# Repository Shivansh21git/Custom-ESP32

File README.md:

# 🚀 Custom ESP32 Development Board – Designed in KiCad

Welcome to the hardware design repo of a **fully custom ESP32-WROOM-32 development board**, engineered for rapid prototyping, compact integration, and modern embedded applications. Designed from the ground up using **KiCad**, this board blends functionality, minimalism, and scalability in one neat package.

---

## ✨ Key Features

- 🔌 **USB Type-C** interface with ESD protection and auto-reset
- 📡 **ESP32-WROOM-32** SoC (Wi-Fi + BLE, dual-core MCU)
- 🔋 **Onboard 3.3V LDO** regulator for stable low-noise operation
- 🎛️ **Accessible I/O headers**: UART, SPI, I2C, ADC, DAC, and GPIOs
- 📐 **Compact PCB layout** – Breadboard compatible
- 🛡️ **Proper antenna clearance & keep-out zone**
- 💾 Designed 100% in **KiCad 7.x**

---

## 🧠 Technical Overview

| Component         | Details                                             |
|------------------|-----------------------------------------------------|
| **MCU**          | ESP32-WROOM-32 (ESP32-D0WDQ6)                       |
| **USB Interface**| USB-C (via CH340/CP2102 + reset circuit)            |
| **Power Input**  | 5V via USB-C                                        |
| **Voltage Reg.** | AP2112 / AMS1117-3.3 LDO Regulator                  |
| **Reset Circuit**| BOOT & EN push buttons with RC logic                |
| **Connectivity** | UART, I2C, SPI, ADC, DAC, PWM exposed               |
| **Mounting**     | 2x M2 screw holes for enclosure compatibility       |
| **Board Size**   | ~74mm x 32mm                                        |

---

---

## 🛠️ Getting Started

### 🖥️ Open Project
- Clone this repo and open `custom_esp32.kicad_pro` in **KiCad 7.x**

### 🧾 Generate Gerbers
- Go to **File → Plot** → Generate files for your PCB manufacturer

### 🔧 Program the Board
- Use Arduino IDE / ESP-IDF
- Connect via USB-C
- Use `BOOT` + `EN` buttons for flashing if needed

---

## 📦 Fabrication Tips

- Board designed with **antenna clearance**
- Clean **silkscreen labeling** for easy assembly
- No component under USB port for low-profile casing
- Test points can be added if needed for production

---

## 💡 Applications

- IoT Device Development
- Sensor Gateway Nodes
- Home Automation
- Robotics Controller
- Custom Wireless Modules

---

## 🤝 Credits & Contact

Designed by **Shivansh Chauhan**  
📧 Email: `shivanshchauhan.228@gmail.com`  
🔗 LinkedIn: https://www.linkedin.com/in/shivanshchauhan2001

If you like this project, consider giving it a ⭐ on GitHub!

---

> “Great hardware begins with thoughtful design.”

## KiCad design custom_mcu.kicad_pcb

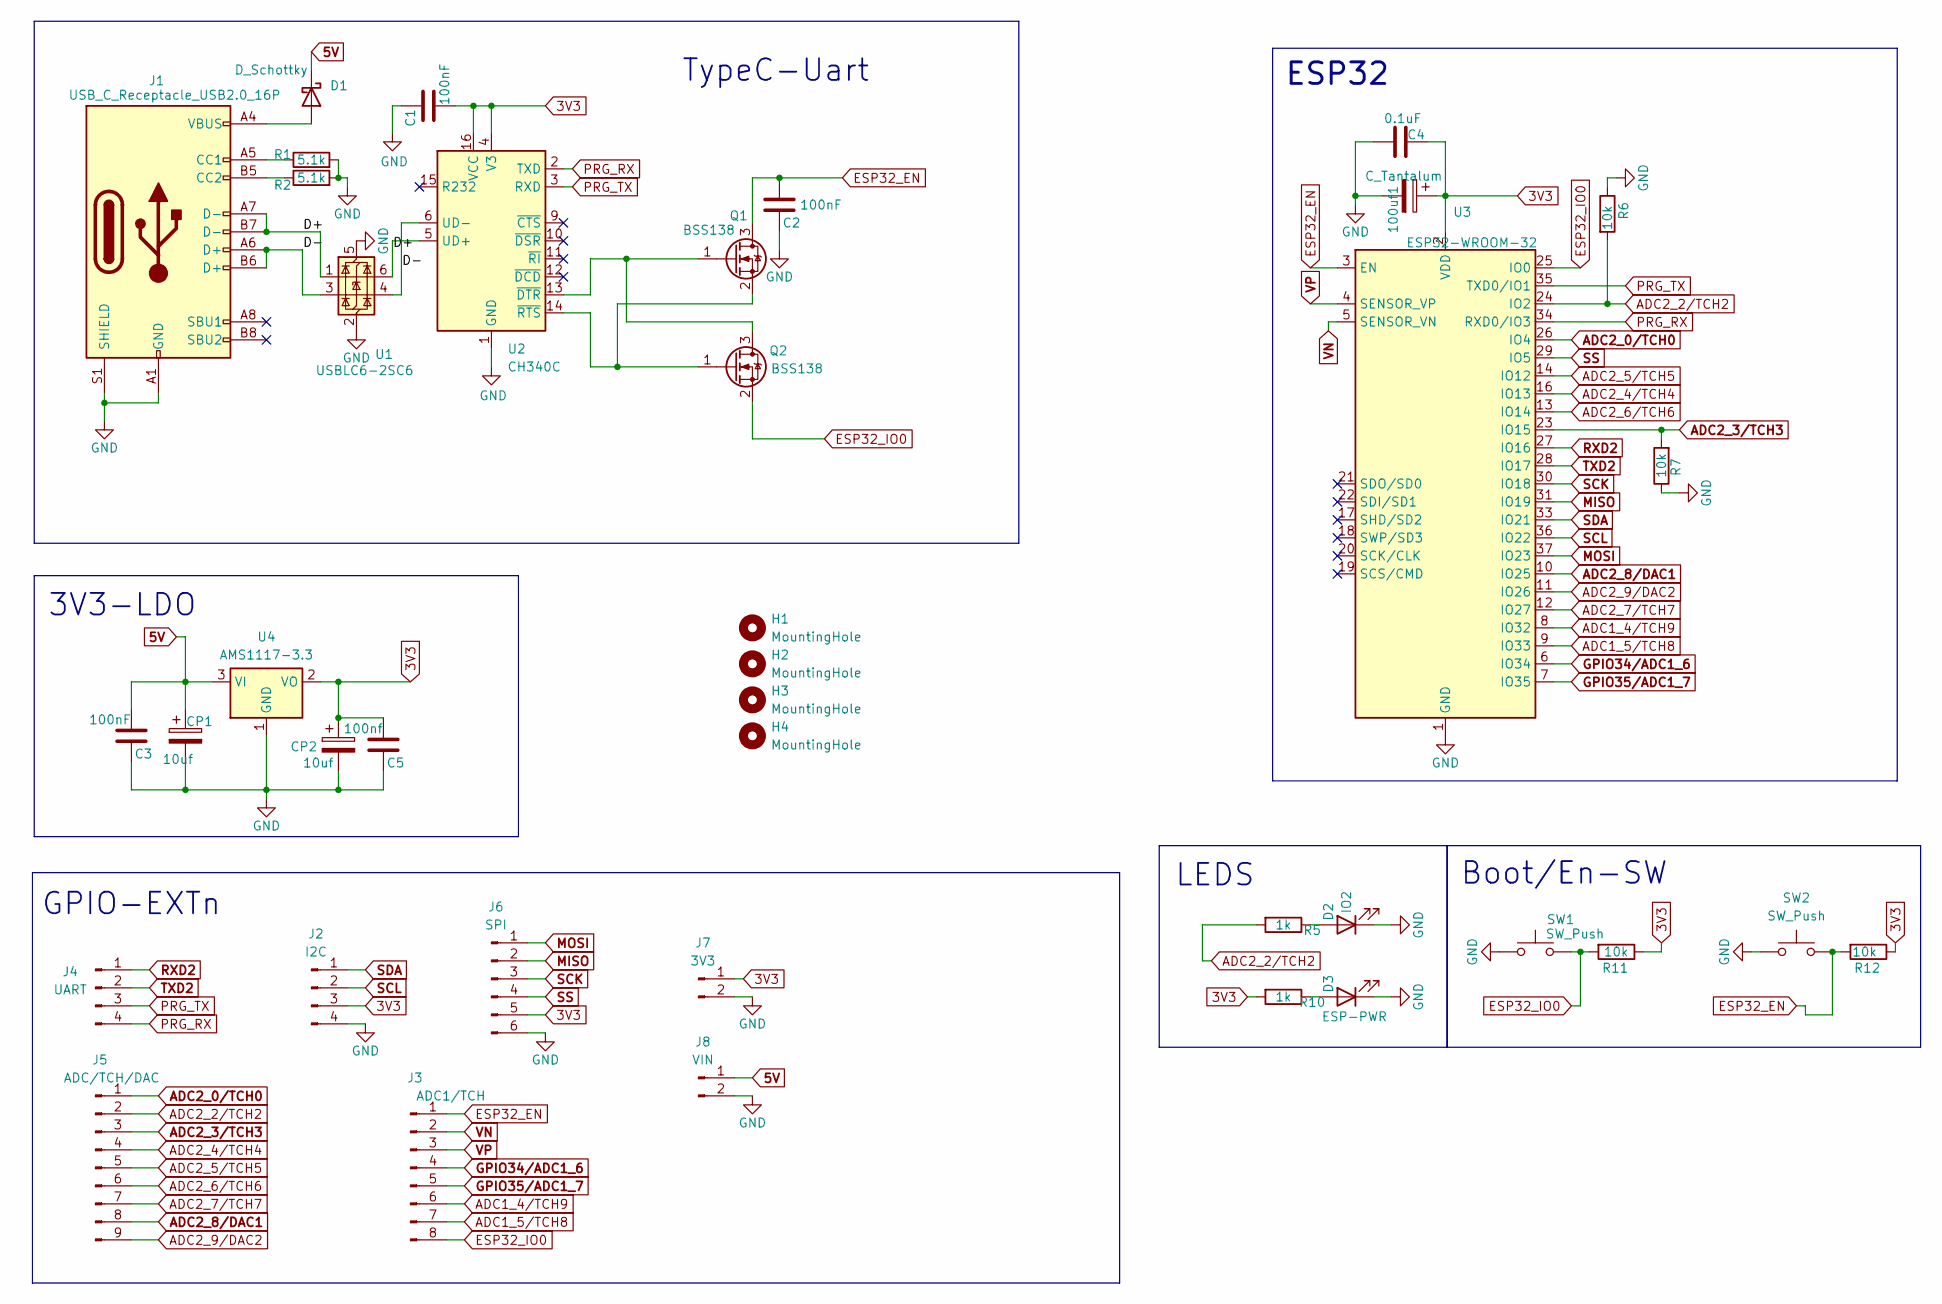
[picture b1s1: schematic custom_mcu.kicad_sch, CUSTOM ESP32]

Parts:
100uf1: C_Tantalum; CP_EIA-3216-10_Kemet-I
C1, C2, C3: 100nF; C_0805_2012Metric_Pad1.18x1.45mm_HandSolder
C4: 0.1uF; C_0805_2012Metric_Pad1.18x1.45mm_HandSolder
C5: 100nf; C_0805_2012Metric_Pad1.18x1.45mm_HandSolder
CP1, CP2: 10uf; C_0805_2012Metric_Pad1.18x1.45mm_HandSolder
D1: D_Schottky; R_0805_2012Metric_Pad1.20x1.40mm_HandSolder
D2: IO2; LED_0805_2012Metric_Pad1.15x1.40mm_HandSolder
D3: ESP-PWR; LED_0805_2012Metric_Pad1.15x1.40mm_HandSolder
H1, H2, H3, H4: MountingHole; MountingHole_2.2mm_M2
J1: USB_C_Receptacle_USB2.0_16P; USB_C_Receptacle_GCT_USB4105-xx-A_16P_TopMnt_Horizontal
J2: I2C; PinHeader_1x04_P2.54mm_Vertical
J3: ADC1/TCH; PinHeader_1x08_P2.54mm_Vertical
J4: UART; PinHeader_1x04_P2.54mm_Vertical
J5: ADC/TCH/DAC; PinHeader_1x09_P2.54mm_Vertical
J6: SPI; PinHeader_1x06_P2.54mm_Vertical
J7: 3V3; PinHeader_1x02_P2.54mm_Vertical
J8: VIN; PinHeader_1x02_P2.54mm_Vertical
Q1, Q2: BSS138; SOT-23
R1, R2: 5.1k; R_0805_2012Metric_Pad1.20x1.40mm_HandSolder
R5, R10: 1k; R_0805_2012Metric_Pad1.20x1.40mm_HandSolder
R6, R7, R11, R12: 10k; R_0805_2012Metric_Pad1.20x1.40mm_HandSolder
SW1, SW2: SW_Push; SW_Tactile_SPST_NO_Straight_CK_PTS636Sx25SMTRLFS
U1: USBLC6-2SC6; SOT-23-6
U2: CH340C; SOIC-16_3.9x9.9mm_P1.27mm
U3: ESP32-WROOM-32
U4: AMS1117-3.3; SOT-223-3_TabPin2

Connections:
3V3: 100uf1.1, C1.2, C4.2, C5.2, CP2.1, J2.3, J6.5, J7.1, R10.2, R11.1, R12.1, U2.4 (V3), U2.16 (VCC), U3.2 (VDD), U4.2 (VO)
5V: C3.2, CP1.1, D1.1 (K), J8.1, U4.3 (VI)
/D+: J1.A7 (D-), J1.B7 (D-), U1.1 (I/O1), U1.6 (I/O1), U2.5 (UD+)
/D-: J1.A6 (D+), J1.B6 (D+), U1.3 (I/O2), U1.4 (I/O2), U2.6 (UD-)
ADC1_4/TCH9: J3.6, U3.8 (IO32)
ADC1_5/TCH8: J3.7, U3.9 (IO33)
ADC2_0/TCH0: J5.1, U3.26 (IO4)
ADC2_2/TCH2: J5.2, R5.2, R6.2, U3.24 (IO2)
ADC2_3/TCH3: J5.3, R7.2, U3.23 (IO15)
ADC2_4/TCH4: J5.4, U3.16 (IO13)
ADC2_5/TCH5: J5.5, U3.14 (IO12)
ADC2_6/TCH6: J5.6, U3.13 (IO14)
ADC2_7/TCH7: J5.7, U3.12 (IO27)
ADC2_8/DAC1: J5.8, U3.10 (IO25)
ADC2_9/DAC2: J5.9, U3.11 (IO26)
ESP32_EN: C2.2, J3.1, Q1.3 (D), R12.2, SW2.2, U3.3 (EN); also elsewhere on the board
ESP32_IO0: J3.8, Q2.2 (S), R11.2, SW1.2, U3.25 (IO0)
GND: 100uf1.2, C1.1, C2.1, C3.1, C4.1, C5.1, CP1.2, CP2.2, D2.1 (K), D3.1 (K), J1.A1 (GND), J1.A12 (GND), J1.B1 (GND), J1.B12 (GND), J1.S1 (SHIELD), J2.4, J6.6, J7.2, J8.2, R1.2, R2.2, R6.1, R7.1, SW1.1, SW2.1, U1.2 (GND), U1.5 (VBUS), U2.1 (GND), U3.1 (GND), U3.15 (GND), U3.38 (GND), U3.39 (GND), U4.1 (GND); also elsewhere on the board
GPIO34/ADC1_6: J3.4, U3.6 (IO34)
GPIO35/ADC1_7: J3.5, U3.7 (IO35)
MISO: J6.2, U3.31 (IO19)
MOSI: J6.1, U3.37 (IO23)
unnamed: D1.2 (A), J1.A4 (VBUS), J1.A9 (VBUS), J1.B4 (VBUS), J1.B9 (VBUS)
unnamed: D2.2 (A), R5.1
unnamed: D3.2 (A), R10.1
unnamed: J1.A5 (CC1), R1.1
unnamed: J1.B5 (CC2), R2.1
unnamed: Q1.1 (G), Q2.3 (D), U2.13 (~DTR)
unnamed: Q1.2 (S), Q2.1 (G), U2.14 (~RTS)
PRG_RX: J4.4, U2.2 (TXD), U3.34 (RXD0/IO3)
PRG_TX: J4.3, U2.3 (RXD), U3.35 (TXD0/IO1)
RXD2: J4.1, U3.27 (IO16)
SCK: J6.3, U3.30 (IO18)
SCL: J2.2, U3.36 (IO22)
SDA: J2.1, U3.33 (IO21)
SS: J6.4, U3.29 (IO5)
TXD2: J4.2, U3.28 (IO17)
VN: J3.2, U3.5 (SENSOR_VN)
VP: J3.3, U3.4 (SENSOR_VP)

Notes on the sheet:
Boot/En-SW
GPIO-EXTn
3V3-LDO
TypeC-Uart
LEDS
ESP32

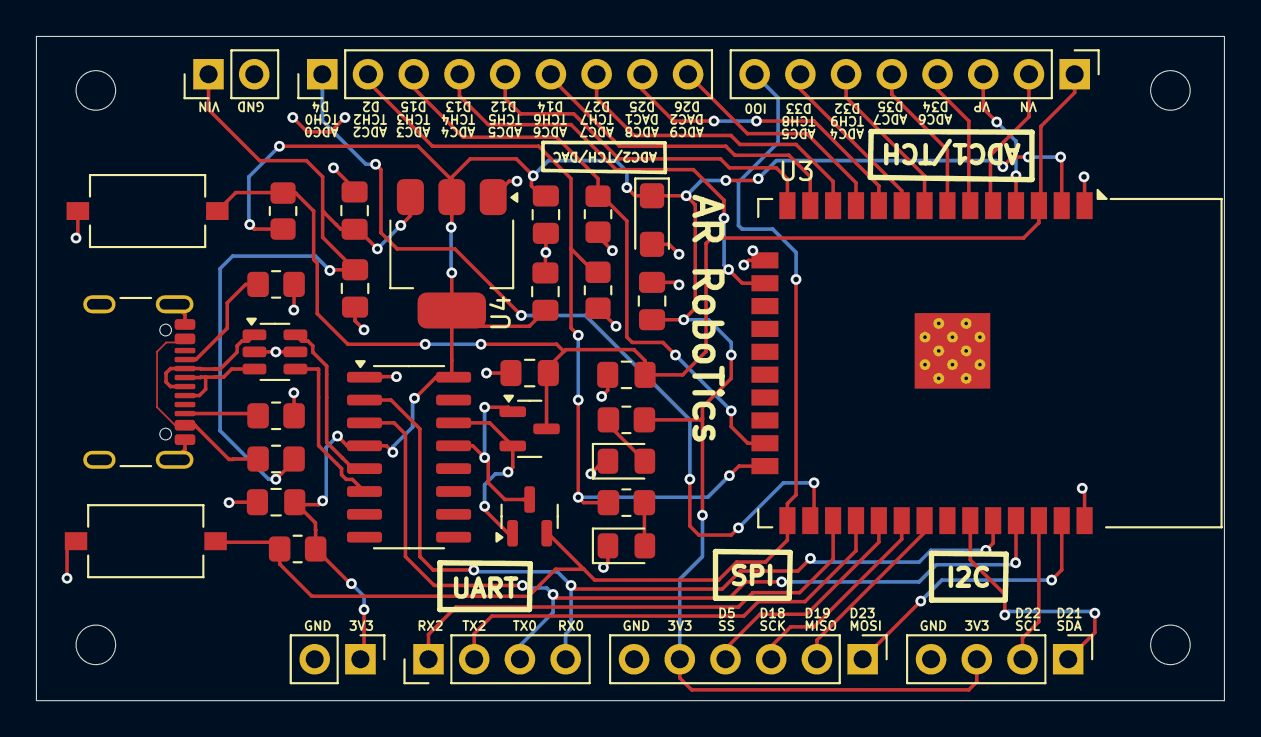
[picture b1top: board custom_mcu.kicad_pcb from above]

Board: 2 copper layers, 66.0 x 36.9 mm, 40 parts (0 on the bottom side), 39 nets.

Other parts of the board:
C2#2: 100nF; C_0805_2012Metric_Pad1.18x1.45mm_HandSolder

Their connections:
ESP32_EN: C2#2.2; also elsewhere on the board
GND: C2#2.1; also elsewhere on the board
